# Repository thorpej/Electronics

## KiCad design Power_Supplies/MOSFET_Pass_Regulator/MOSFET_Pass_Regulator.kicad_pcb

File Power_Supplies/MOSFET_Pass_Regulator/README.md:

# MOSFET Pass Regulator

This is a regulator circuit intended for high voltage / low current applications (i.e. tube circuits)
with simple voltage regulation and ripple filtering requirements.  It has a provision for a power
resistor in series with the MOSFET drain in order to share some of the dissipation burden.

The circuit consists of a voltage divider, a series dropping resistor, a filter capacitor, and a
MOSFET pass element.  Both the upper and lower legs of the voltage divider each consist of
a pair of series resistors and another resistor in parallel to the series pair.  This combination of
3 resistors in each leg should provide sufficient flexibility for just about any configuration.  If
needed, flying leads to a potentiometer could also be used to dial-in a precise voltage.  A 1µF
630V film capacitor takes filters the gate voltage; when used in combination with a relatively
high-value upper voltage divider leg, a significant amount of ripple filtering can be achieved.

## Parts you'll need to build the board

There are a few specific components required to properly assemble this board.

* A TO-220 power MOSFET with a GDS pin configuration.  Pick a MOSFET with a suitable Vds rating; examples include IRF820 (500V), STF16N50M2 / STP16N50M2 (550V), or IXTP8N70X2M (700V).  The STF16N50M2 / STP16N50M2 is my go-to for most applications.
* An Aavid Thermalloy ML33G TO-220 heatsink, available from Mouser.  This heatsink has a flat back that sits right at the edge of the board, to give you the option to mount the board to the chassis by the heatsink itself.
* Panasonic ECW-FE2J105J 630V 1µF radial film capacitor, avaiable from Mouser, or equivalent.
* (Optional) Vishay Dale RS-series 10W wire-wound power resistor, if the application calls for it.  The board may accept other wire-wound power resistors, but the RS-series are what I used on mine, so your mileage may vary.
* (Optional) TE AMP 282843-3 screw terminal block, available from Mouser or Digi-Key.  You can opt to solder flying leads to the pads instead.

In addition, you'll need a few other parts based on your chosen configuration.  See the next
section.

## Example configurations

The following examples are meant to demonstrate this simple board's flexiiblity in a variety of
applications.  Please note the following component assignments (see schematic):

* Vin - Input supply from power rail
* Vout - Output from MOSFET source
* GND - Ground connection
* R1 - Upper voltage divider leg (between Vin and GND)
* R2 - Lower voltage divider leg (between Vin and GND)
* R3 and R4 - Series resistors in parallel with R1
* R5 and R6 - Series resistors in parallel with R2
* R7- Power resistor in series between Vin and MOSFET drain

### Capacitance Multiplier / ripple filter

This is probably the simplest configuration of the board, used simply to provide power supply
ripple filtering using a low-value capacitor.  You only need to select an appropriate resistor for
R1 in order to set the cut-off point of the low-pass filter.  For example, a 200K resistor would
set the cut-off point of the low pass filter to approx. 0.8Hz, which will provide a signifant amount
of filtering.  Install a wire jumper in place of R7, and the board is ready for use.

Note that if your peak-to-peak ripple voltage is greater than your MOSFET's
Vgs threshold voltage, you will need to use a different configuration to drop
more voltage across the MOSFET.

### Zener-referenced Regulator

In this configuration, Zener diodes are used in the bottom leg of the voltage divider to set the
output voltage of the regulator.  Use either a single Zener in the R2 position or two Zeners in
series in the R5 and R6 positions.  The output voltage will be the summed Zener voltages minus
the MOSFET Vgs threshold voltage.  Place a resistor in position R1 to set the current (make sure
sufficient current is avaiable for the Zeners to regulate properly, without exceeding the Zener's
power rating).  The film capacitor will filter ripple as in the Capacitance Multiplier configuration,
as well as shunt Zener noise.

In this configuration, depending on how much voltage is being dropped by the MOSFET, it may
be useful to install a power resistor in position R7 to take some dissipation load off the MOSFET
at higher current levels.  Otherwise, install a wire jumper in place of R7.

As an example, consider a Vin of 600V, and a nominal Vout of 400V, with a steady current load of 20mA.
2 1N5388BG 200V 5W Zener diodes would be installed at R5 and R6, and a 100K resistor installled
at R1.  An 8.2K 10W power resistor is installed at R7.  R1 will dissipate 400mW (use a 1W-rated
part).  The Zeners in the R5 and R6 positions will also each dissipate 400mW.    R7 will dissipate
3.28W and drop 164V, meaning that the voltage at the MOSFET drain will be 436V.  The MOSFET
will drop ~38V (36V + Vgs) and dissipate 760mW.  Vout will be 398V.

### Floating / Proportional Regulator

This is similar to the Zener-referenced Regulator, but rather than using a fixed reference voltage,
a voltage divider is used to set the gate voltage of the MOSFET.  In this way, the output of the
regulator "floats" up and down with Vin, maintaining Vout as a fixed proportion of Vin.  Output
voltage will be the voltage at the junction of the voltage divider minus the MOSFET Vgs threshold
voltage.

In this configuration, depending on how much voltage is being dropped by the MOSFET, it may
be useful to install a power resistor in position R7 to take some dissipation load off the MOSFET
at higher current levels.  Otherwise, install a wire jumper in place of R7.

As an example, consider a Vin of 600V and a nominal Vout of 300V, with a current load that fluctuates
between 2mA and 30mA.  2 330K 1% resistors would be installed at R1 and R2.  A 4.7K 10W power
resistor is installed at R7.  R1 and R2 will dissipate 272mW and set the gate voltage at 300V.

At the low end of the current range (2mA):
* R7 will dissipate 18mW and drop 9.4V.   288.6 (577mW)
* The MOSFET will dissipate 577 mW and drop ~288.6V.

At the high end of the current range (30mA):
* R7 will dissipate 4.23W and drop 141V.
* The MOSFET will dissipate 4.7W and drop 157V

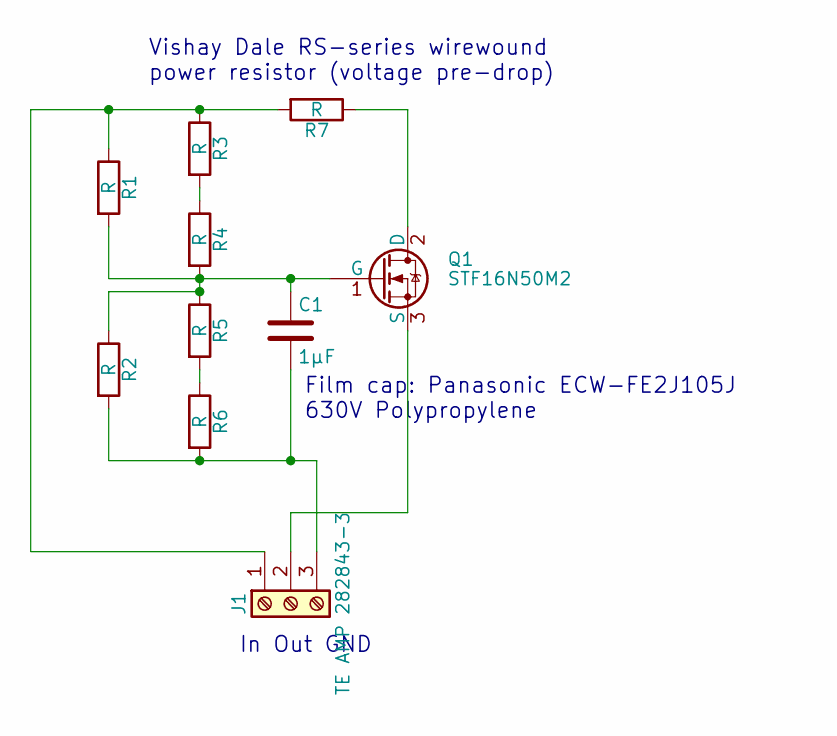
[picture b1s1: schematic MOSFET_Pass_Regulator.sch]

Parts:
C1: 1µF; C_Rect_L26.5mm_W10.5mm_P22.50mm_MKS4
J1: TE AMP 282843-3; TerminalBlock_AMP-3_P10.16mm
Q1: STF16N50M2; TO-220-3_Vertical
R1, R2, R3, R4, R5, R6: R; R_Axial_DIN0411_L9.9mm_D3.6mm_P15.24mm_Horizontal
R7: R; R_Axial_Power_L48.0mm_W12.5mm_P55.88mm

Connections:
unnamed: C1.1, Q1.1 (G), R1.2, R2.1, R4.2, R5.1
unnamed: C1.2, J1.3, R2.2, R6.2
unnamed: J1.1, R1.1, R3.1, R7.2
unnamed: J1.2, Q1.3 (S)
unnamed: Q1.2 (D), R7.1
unnamed: R3.2, R4.1
unnamed: R5.2, R6.1

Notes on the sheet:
Film cap: Panasonic ECW-FE2J105J 630V Polypropylene
In Out GND
Vishay Dale RS-series wirewound power resistor (voltage pre-drop)

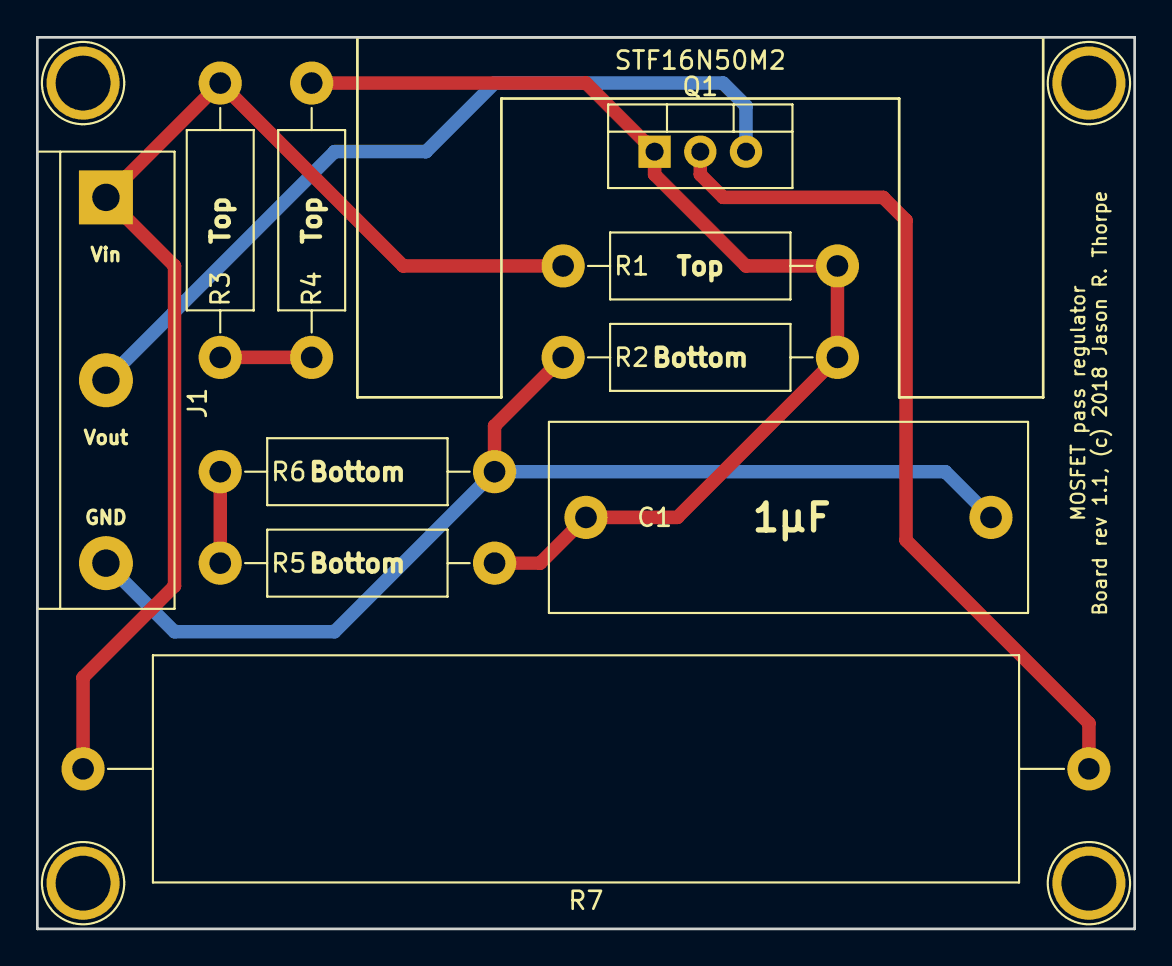
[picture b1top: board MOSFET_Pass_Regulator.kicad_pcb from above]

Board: 2 copper layers, 61.0 x 49.5 mm, 11 parts (0 on the bottom side), 7 nets.

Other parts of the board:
STF16N50M2: Aavid_Thermalloy_ML33G_TO-220-heatsink

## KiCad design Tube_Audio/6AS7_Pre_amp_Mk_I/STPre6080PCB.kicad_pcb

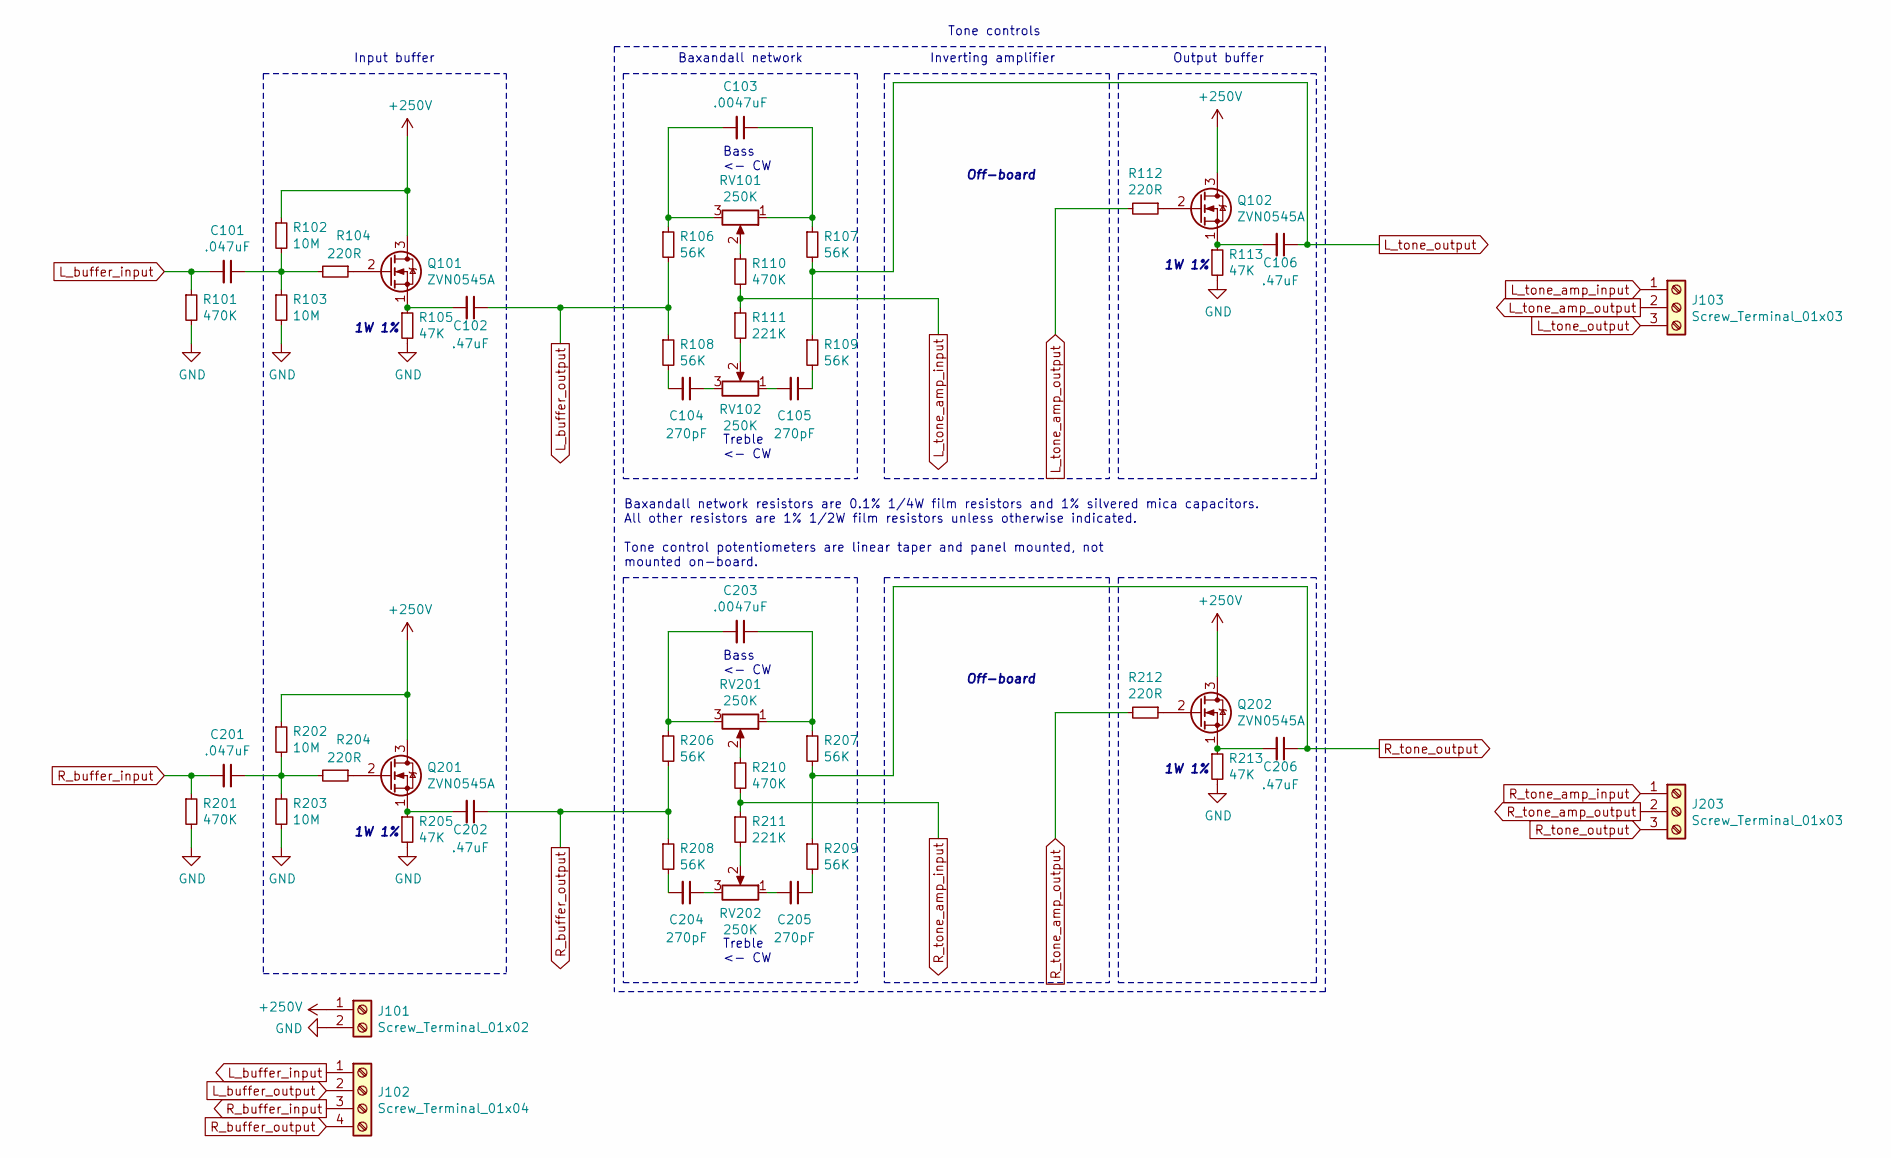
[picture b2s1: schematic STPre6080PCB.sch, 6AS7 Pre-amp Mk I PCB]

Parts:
C101, C201: .047uF; C_Rect_L13.0mm_W5.0mm_P7.50mm; Part Panasonic ECW-FD2J473J4
C102, C106, C202, C206: .47uF; C_Rect_L18.0mm_W8.0mm_P15.00mm_FKS3_FKP3; Part Panasonic ECW-FD2J474JC
C103, C203: .0047uF; C_Rect_L18.0mm_W9.0mm_P8.70mm; Part CDE CD19FD472FO3F
C104, C105, C204, C205: 270pF; C_Rect_L13.0mm_W6.0mm_P5.90mm; Part CDE CD15FD271FO3F
J101: Screw_Terminal_01x02; TerminalBlock_bornier-2_P5.08mm
J102: Screw_Terminal_01x04; TerminalBlock_bornier-4_P5.08mm
J103, J203: Screw_Terminal_01x03; TerminalBlock_bornier-3_P5.08mm
Q101, Q102, Q201, Q202: ZVN0545A; TO-92_Wide
R101, R201: 470K; R_Axial_DIN0414_L11.9mm_D4.5mm_P15.24mm_Horizontal; Part KOA Speer MF1/2DC4703F
R102, R202, R203: 10M; R_Axial_DIN0414_L11.9mm_D4.5mm_P15.24mm_Horizontal; Part Vishay HVR3700001005FR500
R103: 10M; R_Axial_DIN0414_L11.9mm_D4.5mm_P15.24mm_Horizontal; Part HVR3700001005FR500
R104, R112, R204, R212: 220R; R_Axial_DIN0414_L11.9mm_D4.5mm_P15.24mm_Horizontal
R105, R113, R205, R213: 47K; R_Axial_DIN0414_L11.9mm_D4.5mm_P15.24mm_Horizontal; Part TE H4P47KFZA
R106, R107, R108, R109, R206, R207, R208, R209: 56K; R_Axial_DIN0207_L6.3mm_D2.5mm_P10.16mm_Horizontal; Part TE H856KBDA
R110, R210: 470K; R_Axial_DIN0207_L6.3mm_D2.5mm_P10.16mm_Horizontal; Part TE H8470KBZA
R111, R211: 221K; R_Axial_DIN0207_L6.3mm_D2.5mm_P10.16mm_Horizontal; Part TE YR1B221KCC
RV101, RV102, RV201, RV202: 250K; PinHeader_1x03_P2.54mm_Vertical

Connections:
+250V: J101.1, Q101.3 (D), Q102.3 (D), Q201.3 (D), Q202.3 (D), R102.1, R202.1
GND: J101.2, R101.2, R103.2, R105.2, R113.2, R201.2, R203.2, R205.2, R213.2
L_buffer_input: C101.2, J102.1, R101.1
L_buffer_output: C102.1, J102.2, R106.2, R108.1
L_tone_amp_input: J103.1, R110.2, R111.1
L_tone_amp_output: J103.2, R112.2
L_tone_output: C106.1, J103.3, R107.2, R109.1
unnamed: C101.1, R102.2, R103.1, R104.2
unnamed: C102.2, Q101.1 (S), R105.1
unnamed: C103.1, R107.1, RV101.1
unnamed: C103.2, R106.1, RV101.3
unnamed: C104.1, RV102.3
unnamed: C104.2, R108.2
unnamed: C105.1, R109.2
unnamed: C105.2, RV102.1
unnamed: C106.2, Q102.1 (S), R113.1
unnamed: C201.1, R202.2, R203.1, R204.2
unnamed: C202.2, Q201.1 (S), R205.1
unnamed: C203.1, R207.1, RV201.1
unnamed: C203.2, R206.1, RV201.3
unnamed: C204.1, RV202.3
unnamed: C204.2, R208.2
unnamed: C205.1, R209.2
unnamed: C205.2, RV202.1
unnamed: C206.2, Q202.1 (S), R213.1
unnamed: Q101.2 (G), R104.1
unnamed: Q102.2 (G), R112.1
unnamed: Q201.2 (G), R204.1
unnamed: Q202.2 (G), R212.1
unnamed: R110.1, RV101.2
unnamed: R111.2, RV102.2
unnamed: R210.1, RV201.2
unnamed: R211.2, RV202.2
R_buffer_input: C201.2, J102.3, R201.1
R_buffer_output: C202.1, J102.4, R206.2, R208.1
R_tone_amp_input: J203.1, R210.2, R211.1
R_tone_amp_output: J203.2, R212.2
R_tone_output: C206.1, J203.3, R207.2, R209.1

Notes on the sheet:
Input buffer
Baxandall network resistors are 0.1% 1/4W film resistors and 1% silvered mica capacitors. All other resistors are 1% 1/2W film resistors unless otherwise indicated. Tone control potentiometers are linear taper and panel mounted, not mounted on-board.
Tone controls
Inverting amplifier
Baxandall network
Treble <- CW
Bass <- CW
Output buffer
Off-board
1W 1%

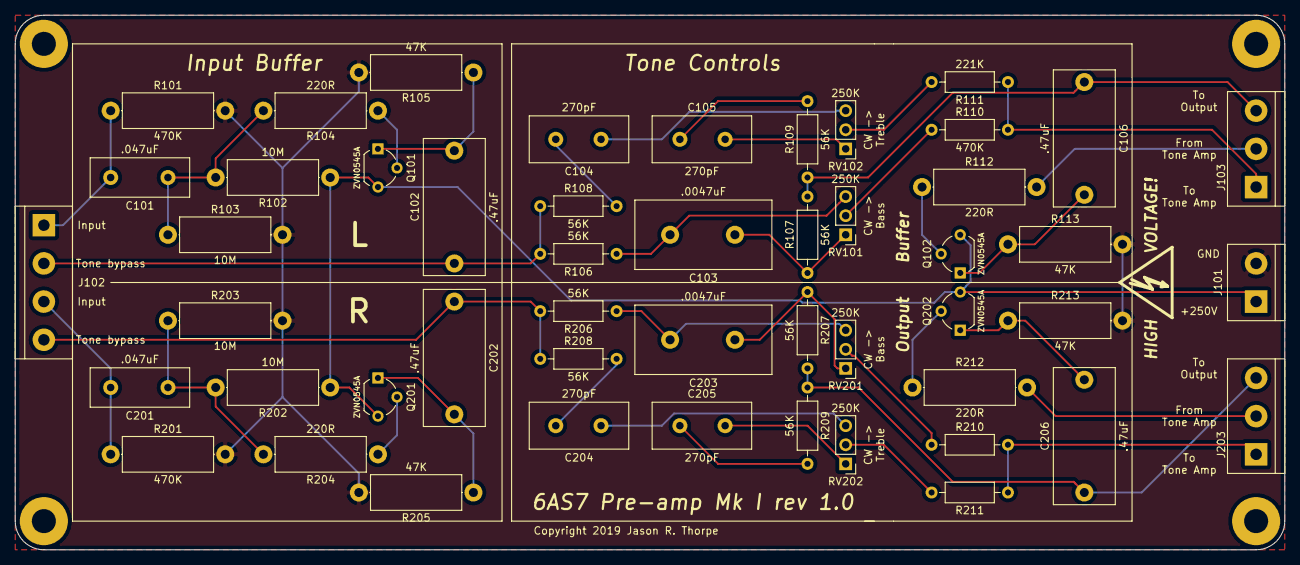
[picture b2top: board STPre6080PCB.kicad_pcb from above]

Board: 2 copper layers, 168.9 x 71.1 mm, 50 parts (0 on the bottom side), 38 nets.

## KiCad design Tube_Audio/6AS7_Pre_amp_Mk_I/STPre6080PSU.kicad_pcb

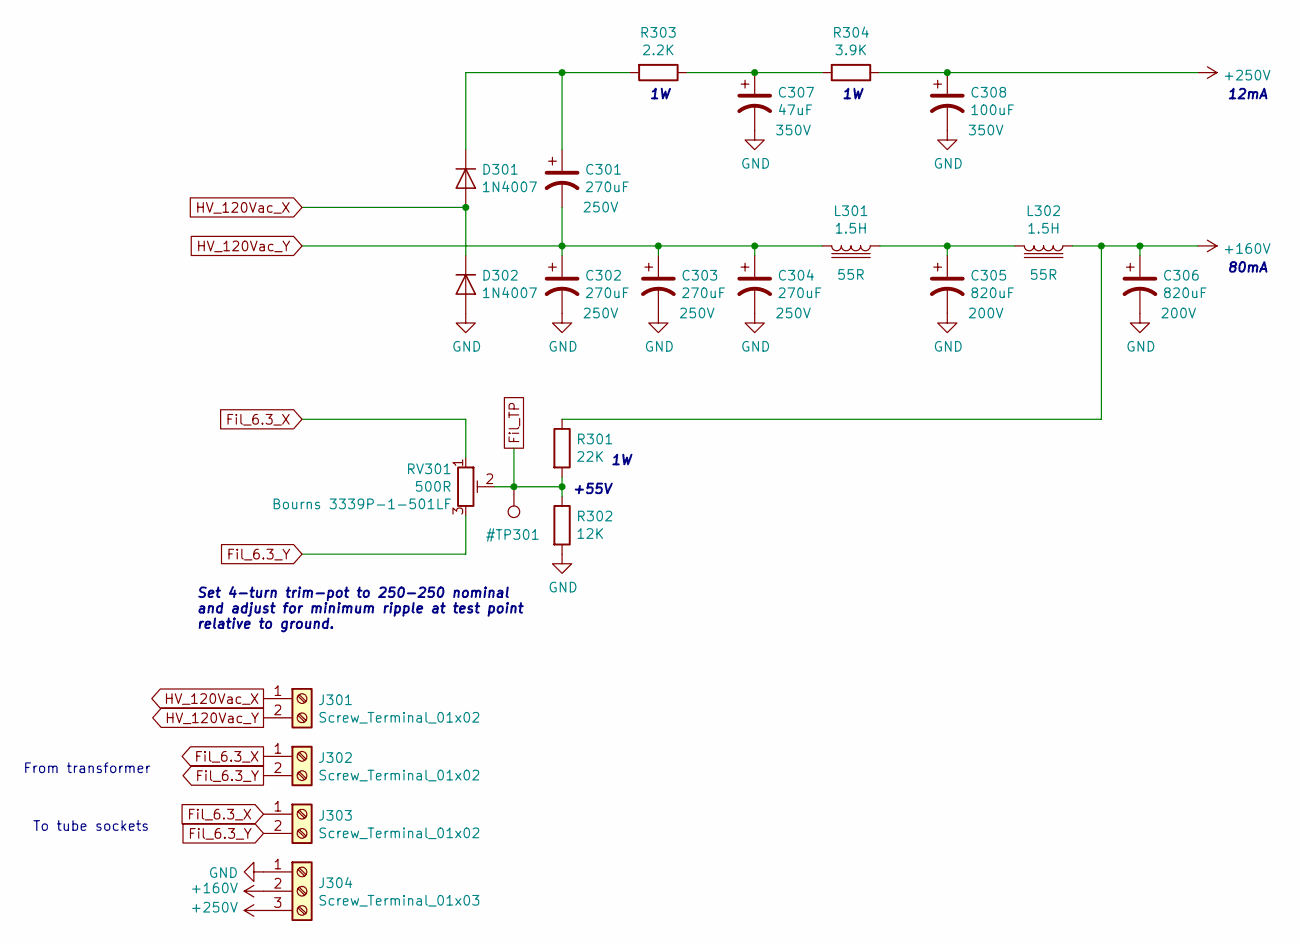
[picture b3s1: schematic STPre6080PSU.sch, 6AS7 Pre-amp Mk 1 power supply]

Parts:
C301, C302, C303, C304: 270uF; CP_Radial_D18.0mm_P7.50mm; Part Nichicon UCY2E271MHD
C305, C306: 820uF; CP_Radial_D25.0mm_P12.50mm; Part Nichicon UPT2D821MRD
C307: 47uF; CP_Radial_D12.5mm_P5.00mm; Part United Chemi-Con EGXF351ELL470MK30S
C308: 100uF; CP_Radial_D18.0mm_P7.50mm; Part Panasonic EEU-EB2V101
D301, D302: 1N4007; D_DO-41_SOD81_P10.16mm_Horizontal
J301, J302, J303: Screw_Terminal_01x02; TerminalBlock_bornier-2_P5.08mm
J304: Screw_Terminal_01x03; TerminalBlock_bornier-3_P5.08mm
L301, L302: 1.5H; TerminalBlock_bornier-2_P5.08mm; Part Triode C354
R301: 22K; R_Axial_DIN0207_L6.3mm_D2.5mm_P7.62mm_Horizontal; Part Vishay / BC PR01000102202JR500
R302: 12K; R_Axial_DIN0207_L6.3mm_D2.5mm_P7.62mm_Horizontal; Part Vishay / BC SFR16S0001202JA500
R303: 2.2K; R_Axial_DIN0207_L6.3mm_D2.5mm_P7.62mm_Horizontal; Part Vishay / BC PR01000102201JA100
R304: 3.9K; R_Axial_DIN0207_L6.3mm_D2.5mm_P7.62mm_Horizontal; Part Vishay / BC PR01000103901JR500
RV301: 500R; Potentiometer_Bourns_3339P_Vertical_HandSoldering; Part Bourns 3339P-1-501LF

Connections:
+160V: C306.1, J304.2, L302.1, R301.1
+250V: C308.1, J304.3, R304.1
Fil_6.3_X: J302.1, J303.1, RV301.1
Fil_6.3_Y: J302.2, J303.2, RV301.3
Fil_TP: R301.2, R302.1, RV301.2; also elsewhere on the board
GND: C302.2, C303.2, C304.2, C305.2, C306.2, C307.2, C308.2, D302.2 (A), J304.1, R302.2
HV_120Vac_X: D301.2 (A), D302.1 (K), J301.1
HV_120Vac_Y: C301.2, C302.1, C303.1, C304.1, J301.2, L301.2
unnamed: C301.1, D301.1 (K), R303.2
unnamed: C305.1, L301.1, L302.2
unnamed: C307.1, R303.1, R304.2

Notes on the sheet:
12mA
80mA
+55V
Set 4-turn trim-pot to 250-250 nominal and adjust for minimum ripple at test point relative to ground.
From transformer
To tube sockets

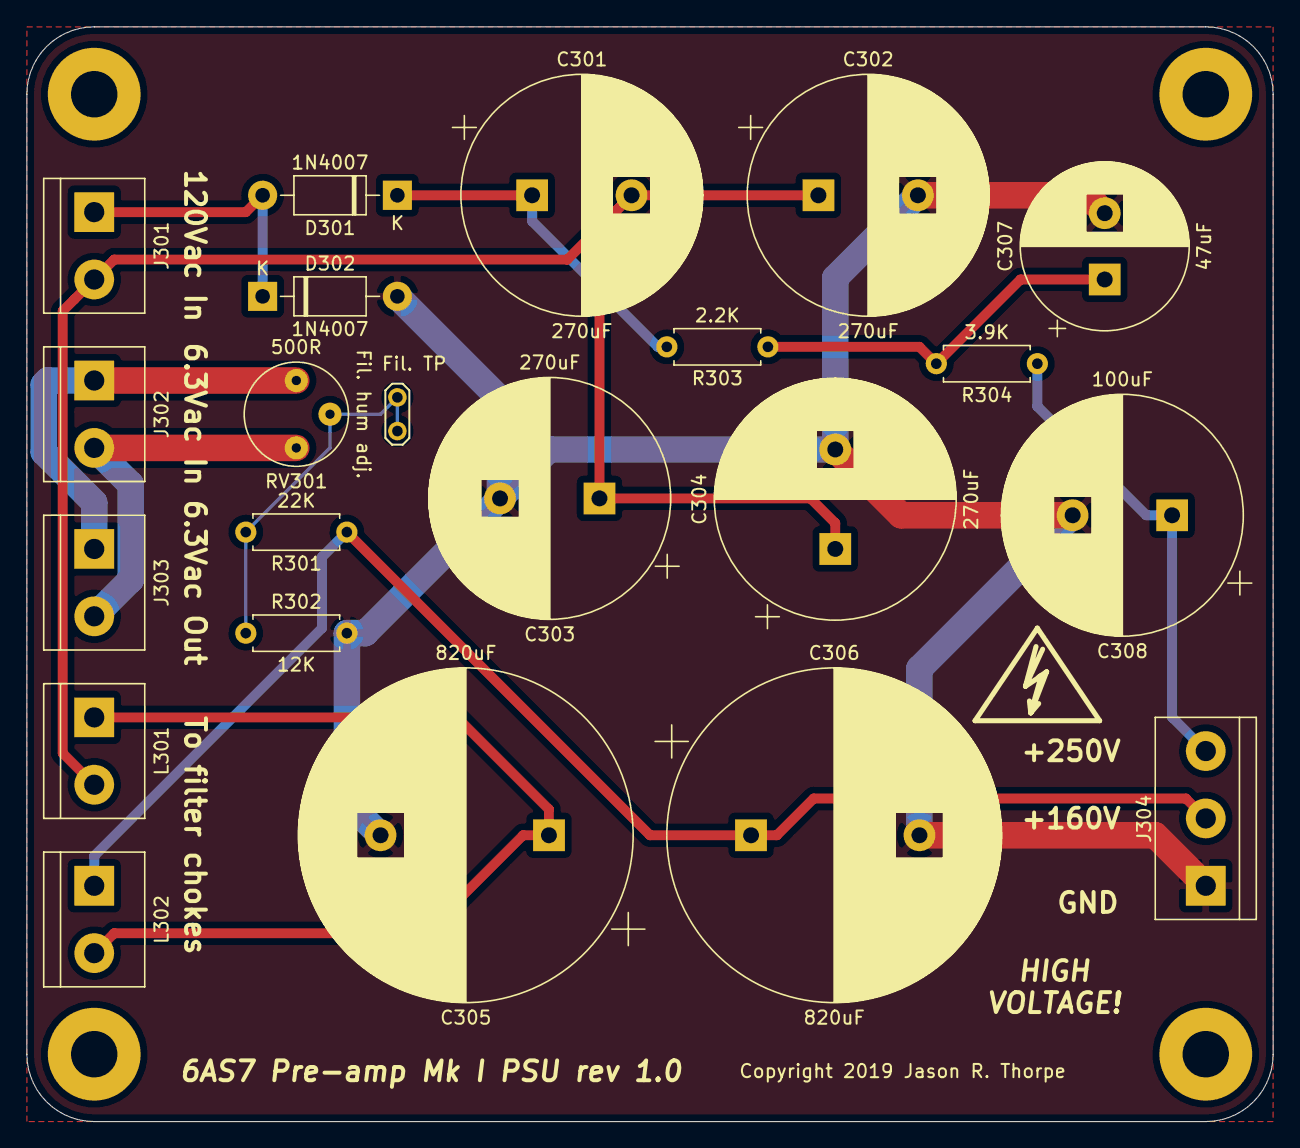
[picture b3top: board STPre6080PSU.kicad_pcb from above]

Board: 2 copper layers, 94.0 x 82.5 mm, 22 parts (0 on the bottom side), 11 nets.

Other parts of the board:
Fil. TP: TestPoint_2Pads_Pitch2.54mm_Drill0.8mm

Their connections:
Fil_TP: Fil. TP.1, Fil. TP.2; also elsewhere on the board

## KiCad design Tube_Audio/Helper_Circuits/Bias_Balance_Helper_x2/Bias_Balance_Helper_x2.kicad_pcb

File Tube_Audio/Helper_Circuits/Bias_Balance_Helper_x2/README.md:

# 2-Channel Bias-Balance Helper

This is a simple helper board that helps simplify the wiring of a particular output tube
bias-balance circuit that I like to use:

	               A
	               |
	      +---R1---+-----C1-)|----+
	      |        |              |
	      |        |              |
	C- ---+       RV1<---R3---RV2-+-GND
	      |        |           ^--+
	      |        |              |
	      +---R2---+-----C2-)|----+
	               |
	               B

Where:
* C- is the input negative bias voltage from the bias supply.
* RV1 is the "balance" pot used to balance the quiescent current of the two output tubes.
* RV2 is the "bias" pot used to set the nominal bias voltage.  The wiper is connected to one end of the pot such that if the wiper fails for some reason, the maxiumum negative bias voltage will be applied to the output tubes, thereby preventing the tubes from melting down.

The circuit is essentially 2 parallel voltage dividers.  The divider for tube "A" is formed by R1,
RV1, R3, and RV2.  The divider for tube "B" formed by R2, RV1, R3, and RV2.  C1 and C2 are
there to smooth any ripple out of the bias voltage applied to the output tube grids.

This little board has connections for GND, C-, and 2 channels worth of R1, R2, C1, and C2.
All that is required finish the complete circuit is to make the appropriate connections to the pots
(RV1 and RV2) whereever they happen to be mounted (usually next to each other on the deck
so it's easy to adjust).  The wiper of RV1 is connected to one end of RV2 with R3, and that can
easily be done directly on the pots themselves.

The resistor footprints on the board can accommodate resistors 2.5mm in diameter; the pad
spacing is 10.16mm.  The capacitor footprints on the board can accommodate  radial electrolytics
up to 10mm in diameter; the lead spacing is 2.5mm.  The electrolytics must have a voltage rating
sufficient for the largest negative voltage your voltage divider network supply will produce.

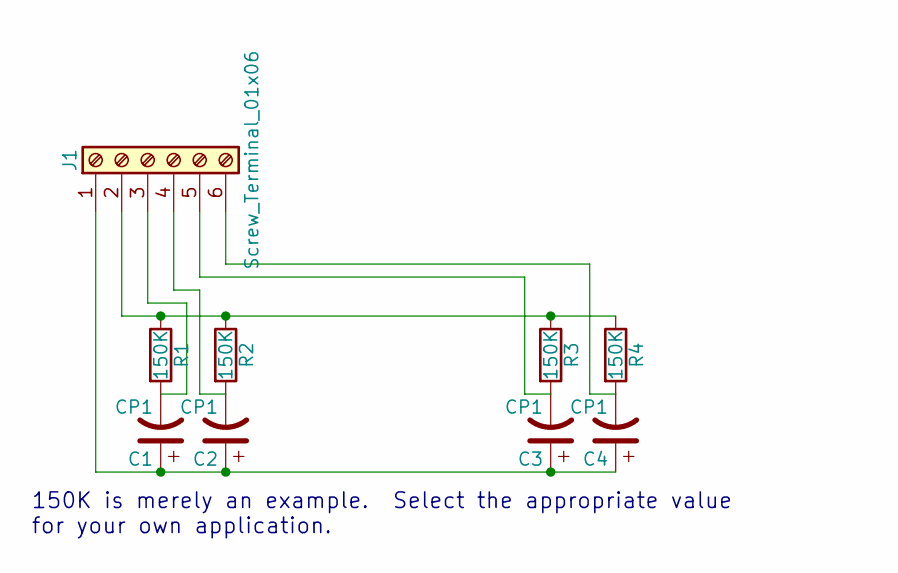
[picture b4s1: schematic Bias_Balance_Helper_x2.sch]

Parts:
C1, C2, C3, C4: CP1; CP_Radial_D10.0mm_P2.50mm
J1: Screw_Terminal_01x06; TerminalBlock_bornier-6_P5.08mm
R1, R2, R3, R4: 150K; R_Axial_DIN0207_L6.3mm_D2.5mm_P10.16mm_Horizontal

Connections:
unnamed: C1.1, C2.1, C3.1, C4.1, J1.1
unnamed: C1.2, J1.3, R1.2
unnamed: C2.2, J1.4, R2.2
unnamed: C3.2, J1.5, R3.2
unnamed: C4.2, J1.6, R4.2
unnamed: J1.2, R1.1, R2.1, R3.1, R4.1

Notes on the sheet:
150K is merely an example. Select the appropriate value for your own application.

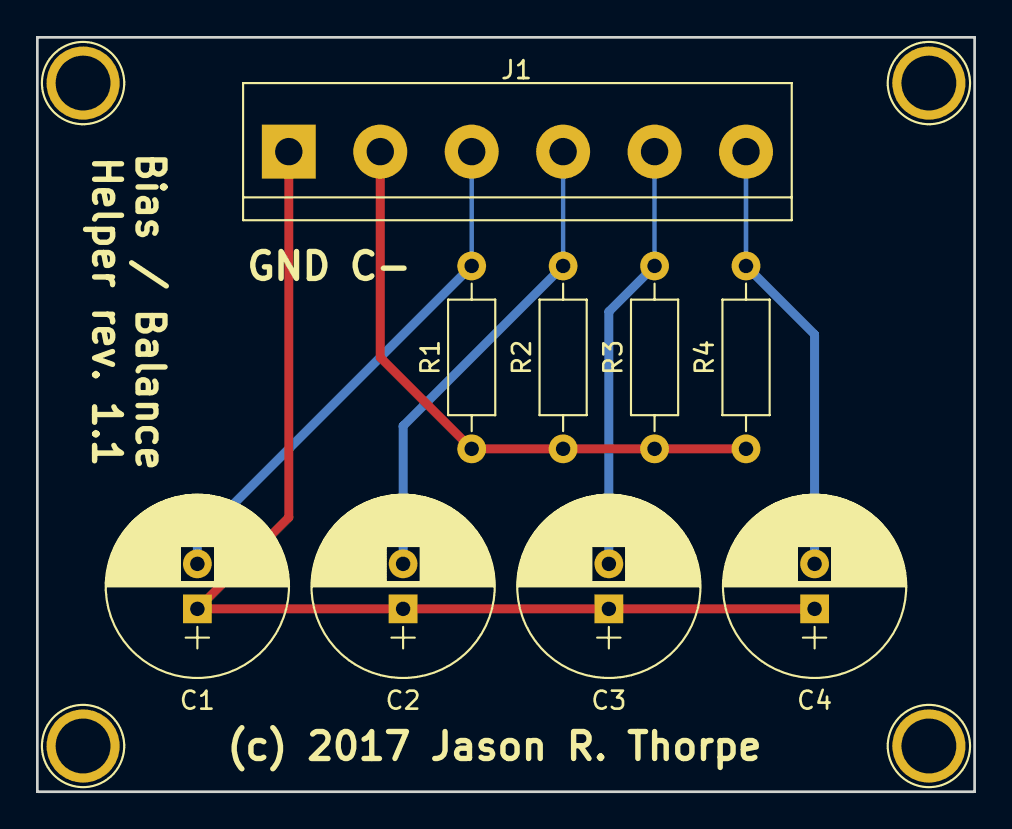
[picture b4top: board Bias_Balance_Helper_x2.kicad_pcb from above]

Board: 2 copper layers, 52.1 x 41.9 mm, 13 parts (0 on the bottom side), 6 nets.

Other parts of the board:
Screw: 1pin
Screw#2, Screw#3, Screw#4: 1pin

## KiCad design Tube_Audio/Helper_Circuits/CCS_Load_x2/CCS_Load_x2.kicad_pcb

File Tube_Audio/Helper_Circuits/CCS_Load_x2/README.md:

# Constant Current Source for plate load

This is a simple solid-state constant current source board intended for
use as a plate load in a triode or pentode voltage gain stage.  It is based
on the IXYS 10M45S 3-pin current regulator.  An IXYS 10M90S can be substituted
if you _really_ need the increased voltatge rating, but I suspect that you
don't.  A CCS plate loads provide a near "infinite" resistance to a loaded
device, resulting in a nearly horizontal load line.  This results in maximized
gain (nearly achieving the mu of the loaded device) and reduced distortion.
I have used this board to provide the plate load for a low-gain Hi-Fi pre-amp
based on power triodes.

This circuit is pretty simple: The high-voltage supply is connected to the
anode of each 10M45S, and the cathode of each 10M45S is connected to one
output channel.  A 1K linear trim pot is provided to dial-in the desired
current for each channel.  The channel's current may be sensed at the 10R 1%
resistor that's in series with the trim pot.

Board space is allocated for heat sinks, but you probably won't need any as
beefy as afforded.  In a typical application, you're dropping less than 200V
across the CCS, at currents less than 7mA.  (I.e. typically less than 1.5
watts.) If you need any heat sink at all, those small fin-type sinks will
probably suffice (that's what I use most of the time).

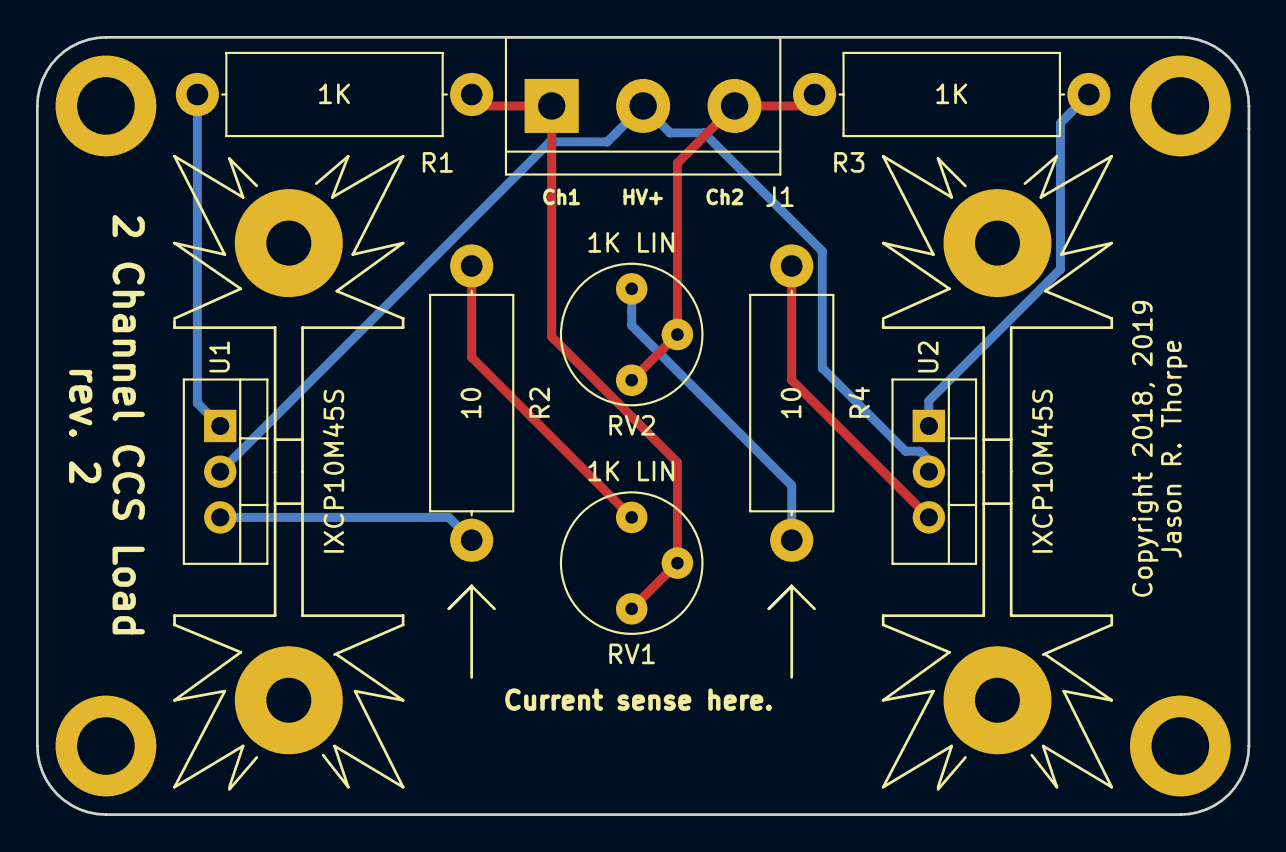
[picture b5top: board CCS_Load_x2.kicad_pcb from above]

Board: 2 copper layers, 67.3 x 43.2 mm, 11 parts (0 on the bottom side), 9 nets.

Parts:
J1: Screw_Terminal_01x03; TerminalBlock_bornier-3_P5.08mm
R1, R3: 1K; R_Axial_DIN0414_L11.9mm_D4.5mm_P15.24mm_Horizontal
R2, R4: 10; R_Axial_DIN0414_L11.9mm_D4.5mm_P15.24mm_Horizontal
RV1, RV2: 1K LIN; Potentiometer_Bourns_3339P_Vertical_HandSoldering
Sink1, Sink1#2: Heatsink_Fischer_SK104-STC-STIC_35x13mm_2xDrill2.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; Heatsink_Fischer_SK104-STC-STIC_35x13mm_2xDrill2.5mm
U1, U2: IXCP10M45S; TO-220-3_Vertical

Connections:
unnamed: J1.1, R1.2, RV1.2, RV1.3
unnamed: J1.2, U1.2, U2.2
unnamed: J1.3, R3.2, RV2.2, RV2.3
unnamed: R1.1, U1.1
unnamed: R2.1, U1.3
unnamed: R2.2, RV1.1
unnamed: R3.1, U2.1
unnamed: R4.1, U2.3
unnamed: R4.2, RV2.1

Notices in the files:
Power_Supplies/MOSFET_Pass_Regulator/MOSFET_Pass_Regulator.kicad_pcb:
Board rev 1.1, (c) 2018 Jason R. Thorpe
Tube_Audio/6AS7_Pre_amp_Mk_I/STPre6080PCB.kicad_pcb:
Copyright 2019 Jason R. Thorpe.  All rights reserved.
Tube_Audio/Helper_Circuits/Bias_Balance_Helper_x2/Bias_Balance_Helper_x2.kicad_pcb:
(c) 2017 Jason R. Thorpe
Tube_Audio/Helper_Circuits/CCS_Load_x2/CCS_Load_x2.kicad_pcb:
Copyright 2018, 2019 Jason R. Thorpe.  All rights reserved.
